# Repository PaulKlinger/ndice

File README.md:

# Compact Universal Electronic Dice

Some hints for anyone trying to build these:

- The PCB should be 0.8mm thick.

- You might have noticed that the two parts of the 3D printed top part that press on the buttons are not symmetric. That's because the smd buttons have a little play on when put into the alignment holes in the PCB (I think the holes on my boards were drilled slightly oversized). I happened to solder the left button a little further in than the right one, and designed the case around that (very professional, I know...).

- The holes over the LEDs in the top cover are filled with some 2mm PMMA fiber optic cable. I bought it [here](https://www.aliexpress.com/item/5mX-Transparent-side-glow-plastic-PMMA-fiber-optic-cable-solid-core-optic-cable-diameter-2mm-3mm/32807597828.html). This kind of fiber is not optimal for this because it glows from the side (which I needed for [this project](https://github.com/PaulKlinger/kerr_geodesic_sculpture)), but most of the light still comes out the end. Getting the fiber into the holes can be kind of tricky, depending on the precise over-/underextrusion of your 3D printer & filament (for me it was a lot easier with the blue than the black ones). I cut the tip of the fiber to a point, push it firmly through so a bit sticks out the other side, and then use pliers to pull it all the way through. Then I cut it flush using some flush cutters. The pliers and cutters invariable leave some scratches so I have to polish the top...

- To get the (3D printed) cap on the potentiometer you need to cut off the top of the knob. The ones mentioned in the BOM have a relatively soft plastic knob, so that's pretty easy. The cap should be a friction fit.

- The battery holder is soldered to the bottom, so that the MCU sits between the bottom of the battery holder and the PCB (the pins should be long enough to still reach through the PCB). Make sure that the battery holder is parallel to the PCB.

- The 3D printed spacers go between the battery holder and the PCB. I glued them to the PCB with superglue. They are mostly there to hide the gap and don't really provide mechanical support.

- The 3D printed top sort of holds in place without glue, but to make sure it sticks I superglued it to the side of the potentiometer by pressing it forward (towards the buttons) and down. This way it can still be removed by pressing in the opposite direction to break the glue.

- The oval hole on the left side of the top cover is used to reprogram the MCU without dissasembling the die. I use a small jig with three spring loaded pogo pins ([bought here](https://www.aliexpress.com/item/50pcs-set-New-P75-B1-Dia-1-02mm-100g-Cusp-Spear-Spring-Loaded-Test-Probes-Pogo/32767984398.html)) to connect to the pads underneath (you need to put some solder in the three holes to make a surface for the pins to push against). The holes are the standard pin header ones, 0.1 inch apart, so you can just solder the pogo pins into three adjacent holes of a protoboard. From the buttons down the three pads are VCC, UPDI data, GND. Here's [a picture](programming_jig.jpg) of the programming jig with a PICkit 4 connected (the PICkit doesn't provide power, so that comes from the usb). (I don't really recommend the pickit, the AVR support is still in beta and there are some irritating bugs.)

I bought all the components except the [ATtiny1614 microcontroller](https://octopart.com/attiny1614-ssfr-microchip-82181131) from Aliexpress. They are, e.g., available here (no guarantee that the links still work):
- [Capacitors (x100) - $1.94](https://www.aliexpress.com/item/100pcs-3-3PF-47UF-0805-SMD-100V-X7R-10-100nf-0-1uf-104K-104-22UF-4/32882102243.html)
- [Resistors (x100) - $0.63](https://www.aliexpress.com/item/100Pcs-0805-SMD-1-4W-0R-10M-chip-resistor-0-10R-100R-220R-330R-470R-1K/32858225842.html)
- [Potentiometers (x10) - $1.41](https://www.aliexpress.com/item/10pcs-x-RV09-vertical-12-5mm-Shaft-5K-10K-50K-100K-0932-Adjustable-Resistor-9-type/32897258726.html)
- [Battery holder (x10) - $0.65](https://www.aliexpress.com/item/10PCS-Battery-Button-Cell-Holder-Socket-Case-CR2032-battery-holder-2032/32819924096.html)
- [LEDs (x100) - $0.55](https://www.aliexpress.com/item/Free-Ship-100PCS-0805-light-emitting-diode-SMD-LED-bead-Red-Yellow-Green-White-Blue-Orange/32871959868.html)
- [switch (x100) - $1.43](https://www.aliexpress.com/item/50pcs-3-6mm-SMD-light-touch-switch-2-pin-side-button-Micro-switch-button-switches-3mm/32311331185.html)

(everything including shipping to Austria)

That's < $0.9 / unit for everything except the microcontroller when building 10 units, and < $1.55 / unit total. (And you have a lot of components left over after building 10, like 80 switches, 40 LEDs, 90 capacitors,...)

If the links above don't work, or you want to buy from more reputable suppliers, check the [octopart bom](pcb/octopart_bom.md).

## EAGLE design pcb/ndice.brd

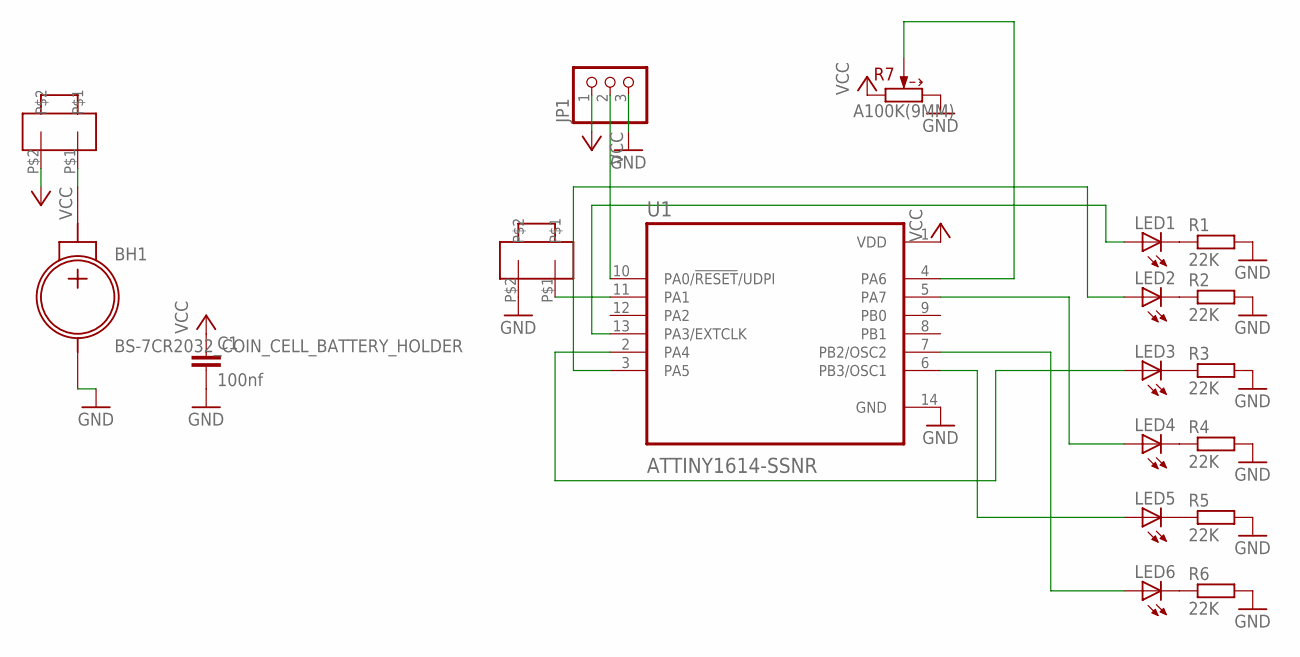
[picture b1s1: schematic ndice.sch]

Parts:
BH1: BS-7CR2032_COIN_CELL_BATTERY_HOLDER; BS-7
C1: 100nf; C0805
JP1: PINHD-1X3CB; 1X03-CLEANBIG
LED1, LED2, LED3, LED4, LED5, LED6: LEDSML0805; SML0805
R1, R2, R3, R4, R5, R6: 22K; R0805
R7: A100K(9MM); RV09-SINGLE
U1: ATTINY1614-SSNR; SOIC127P600X175-14N
U$1, U$2: SIDEBUTTON; SMD

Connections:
GND: BH1.NEG, C1.2, JP1.3, R1.2, R2.2, R3.2, R4.2, R5.2, R6.2, R7.3 (CW), U1.14 (GND), U$2.P$2
unnamed: BH1.POS, U$1.P$1
unnamed: U1.11 (PA1), U$2.P$1
unnamed: JP1.2, U1.10 (PA0/!RESET!/UDPI)
unnamed: LED1.C, R1.1
unnamed: LED2.C, R2.1
unnamed: LED3.C, R3.1
unnamed: LED4.C, R4.1
unnamed: LED5.C, R5.1
unnamed: LED6.C, R6.1
unnamed: LED1.A, U1.13 (PA3/EXTCLK)
unnamed: LED2.A, U1.3 (PA5)
unnamed: LED3.A, U1.2 (PA4)
unnamed: LED4.A, U1.5 (PA7)
unnamed: LED5.A, U1.6 (PB3/OSC1)
unnamed: LED6.A, U1.7 (PB2/OSC2)
unnamed: R7.2 (W), U1.4 (PA6)
VCC: C1.1, JP1.1, R7.1 (CCW), U1.1 (VDD), U$1.P$2

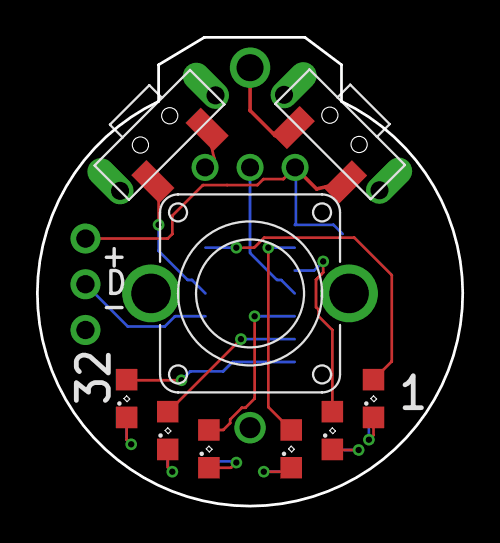
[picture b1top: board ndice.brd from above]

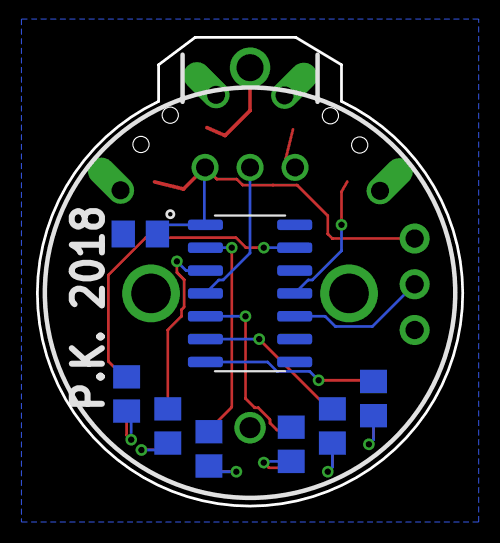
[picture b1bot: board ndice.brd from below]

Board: 2 copper layers, 23.6 x 26.0 mm, 19 parts (9 on the bottom side), 18 nets.

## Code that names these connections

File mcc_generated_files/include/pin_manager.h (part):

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/**
 * \brief Set IO_PB3 input/sense configuration
 *
 * Enable/disable IO_PB3 digital input buffer and pin change interrupt,
 * select pin interrupt edge/level sensing mode
 *
 * \param[in] isc PORT_ISC_INTDISABLE_gc    = Interrupt disabled but input buffer enabled
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/**
 * \brief Set IO_PB2 input/sense configuration
 *
 * Enable/disable IO_PB2 digital input buffer and pin change interrupt,
 * select pin interrupt edge/level sensing mode
 *
 * \param[in] isc PORT_ISC_INTDISABLE_gc    = Interrupt disabled but input buffer enabled
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/**
 * \brief Set IO_PA1 input/sense configuration
 *
 * Enable/disable IO_PA1 digital input buffer and pin change interrupt,
 * select pin interrupt edge/level sensing mode
 *
 * \param[in] isc PORT_ISC_INTDISABLE_gc    = Interrupt disabled but input buffer enabled
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/**
 * \brief Set IO_PA4 input/sense configuration
 *
 * Enable/disable IO_PA4 digital input buffer and pin change interrupt,
 * select pin interrupt edge/level sensing mode
 *
 * \param[in] isc PORT_ISC_INTDISABLE_gc    = Interrupt disabled but input buffer enabled
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/**
 * \brief Set IO_PA3 input/sense configuration
 *
 * Enable/disable IO_PA3 digital input buffer and pin change interrupt,
 * select pin interrupt edge/level sensing mode
 *
 * \param[in] isc PORT_ISC_INTDISABLE_gc    = Interrupt disabled but input buffer enabled
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/**
 * \brief Set IO_PA6 input/sense configuration
 *
 * Enable/disable IO_PA6 digital input buffer and pin change interrupt,
 * select pin interrupt edge/level sensing mode
 *
 * \param[in] isc PORT_ISC_INTDISABLE_gc    = Interrupt disabled but input buffer enabled
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/**
 * \brief Set IO_PA5 input/sense configuration
 *
 * Enable/disable IO_PA5 digital input buffer and pin change interrupt,
 * select pin interrupt edge/level sensing mode
 *
 * \param[in] isc PORT_ISC_INTDISABLE_gc    = Interrupt disabled but input buffer enabled
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/**
 * \brief Set IO_PA7 input/sense configuration
 *
 * Enable/disable IO_PA7 digital input buffer and pin change interrupt,
 * select pin interrupt edge/level sensing mode
 *
 * \param[in] isc PORT_ISC_INTDISABLE_gc    = Interrupt disabled but input buffer enabled
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
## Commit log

2018-12-09 initial commit, working
2019-01-02 use random() instead of rand() to make distribution more even
2019-01-02 shift num_sides to make use of otherwise useless ADC values
2019-01-04 added note about MCC flakiness
2019-01-04 removed obsolete comment
2019-01-04 forgot to commit these files previously...
2019-01-28 moved stuff around
2019-01-28 added 3d printed parts
2019-01-28 added pcb files
2019-01-28 added bom
2019-01-28 added readme
2019-01-28 renamed bom
2019-01-28 updated gerbers
2019-01-28 updated eagle brd file
2019-01-28 corrected video link
2019-01-28 updated video link image
2019-01-28 ignore gerber files for github language detection
2019-02-08 added purchase links for side buttons and potentiometer
2019-02-08 Added battery holder to bom, build tips to readme
2019-02-08 readme tweaks
2019-02-08 added purchase links for all the components
2019-02-08 added octopart bom (by https://github.com/cmcraft)
2019-02-08 added compiled hex file
2019-02-09 Corrected typo

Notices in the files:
mcc_generated_files/include/pin_manager.h:
(c) 2018 Microchip Technology Inc. and its subsidiaries.
